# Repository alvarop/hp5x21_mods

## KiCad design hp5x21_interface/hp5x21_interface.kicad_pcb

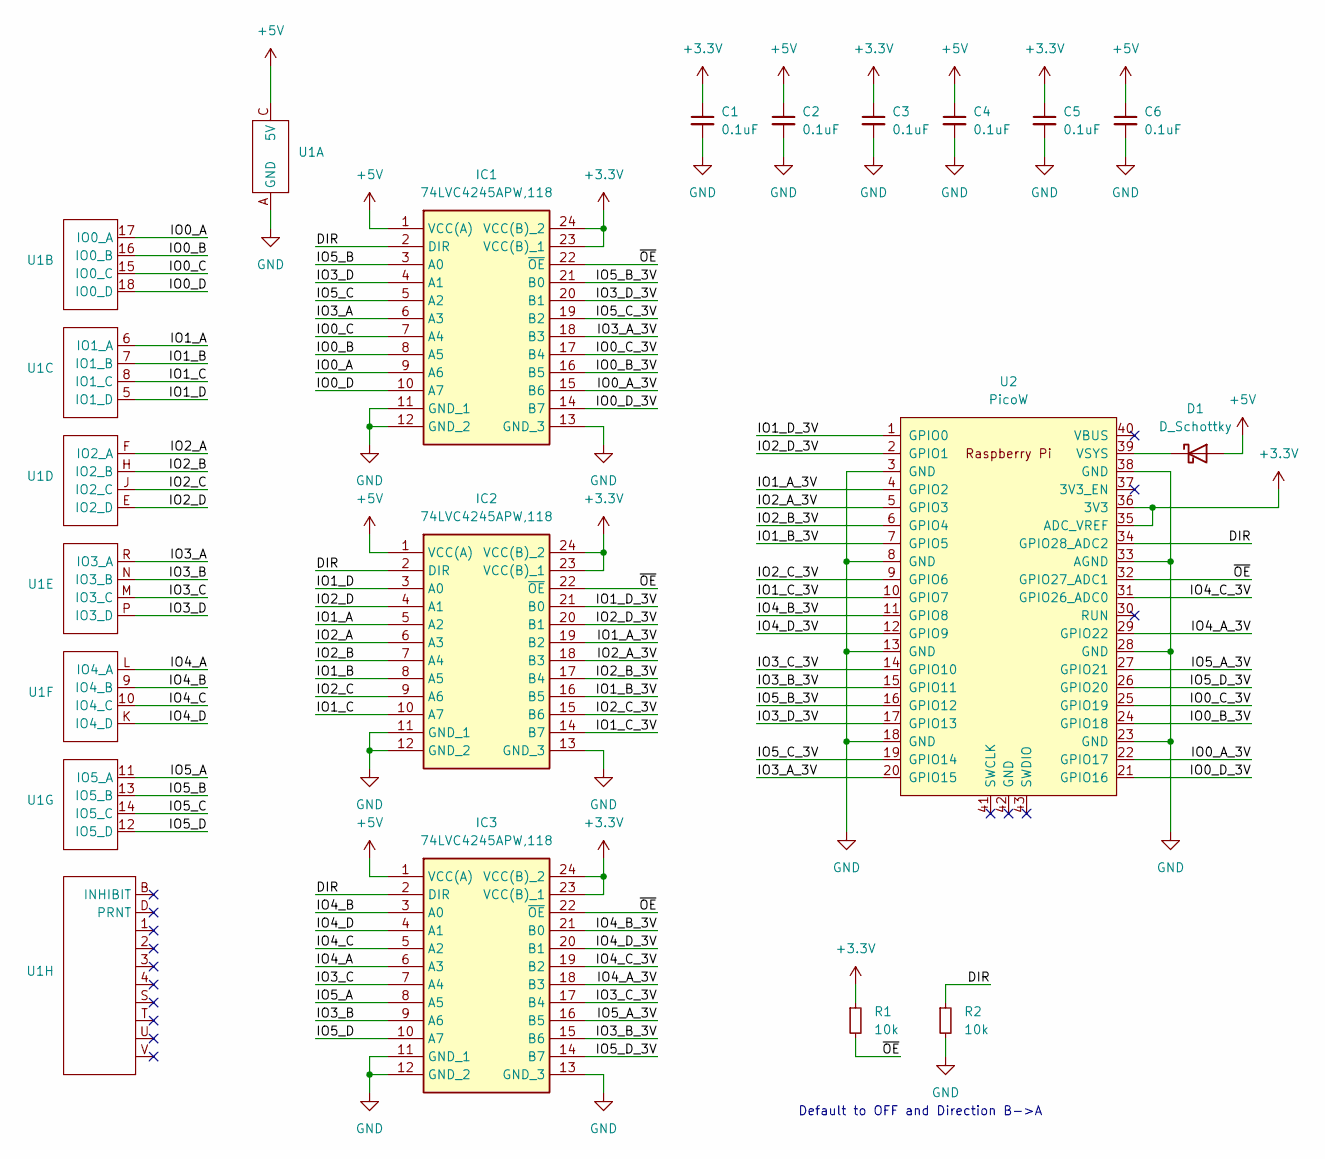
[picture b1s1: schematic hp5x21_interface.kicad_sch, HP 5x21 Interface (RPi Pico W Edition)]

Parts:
C1, C2, C3, C4, C5, C6: 0.1uF; C_0402_1005Metric
D1: D_Schottky; D_SOD-123; MPN MBR0520LT1G
IC1, IC2, IC3: 74LVC4245APW,118; SOP65P640X110-24N; MPN 74LVC4245APW,118
R1, R2: 10k; R_0402_1005Metric
U1: 307-036-520-201; 305-036-520-202; MPN 305-036-520-202
U2: PicoW; RPi_PicoW_SMD_TH; MPN SC0918

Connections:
+3.3V: C1.1, C3.1, C5.1, IC1.23 (VCC(B)_1), IC1.24 (VCC(B)_2), IC2.23 (VCC(B)_1), IC2.24 (VCC(B)_2), IC3.23 (VCC(B)_1), IC3.24 (VCC(B)_2), R1.1, U2.35 (ADC_VREF), U2.36 (3V3)
+5V: C2.1, C4.1, C6.1, D1.2 (A), IC1.1 (VCC(A)), IC2.1 (VCC(A)), IC3.1 (VCC(A)), U1.C (5V)
/DIR: IC1.2 (DIR), IC2.2 (DIR), IC3.2 (DIR), R2.1, U2.34 (GPIO28_ADC2)
/IO0_A: IC1.9 (A6), U1.17 (IO0_A)
/IO0_A_3V: IC1.15 (B6), U2.22 (GPIO17)
/IO0_B: IC1.8 (A5), U1.16 (IO0_B)
/IO0_B_3V: IC1.16 (B5), U2.24 (GPIO18)
/IO0_C: IC1.7 (A4), U1.15 (IO0_C)
/IO0_C_3V: IC1.17 (B4), U2.25 (GPIO19)
/IO0_D: IC1.10 (A7), U1.18 (IO0_D)
/IO0_D_3V: IC1.14 (B7), U2.21 (GPIO16)
/IO1_A: IC2.5 (A2), U1.6 (IO1_A)
/IO1_A_3V: IC2.19 (B2), U2.4 (GPIO2)
/IO1_B: IC2.8 (A5), U1.7 (IO1_B)
/IO1_B_3V: IC2.16 (B5), U2.7 (GPIO5)
/IO1_C: IC2.10 (A7), U1.8 (IO1_C)
/IO1_C_3V: IC2.14 (B7), U2.10 (GPIO7)
/IO1_D: IC2.3 (A0), U1.5 (IO1_D)
/IO1_D_3V: IC2.21 (B0), U2.1 (GPIO0)
/IO2_A: IC2.6 (A3), U1.F (IO2_A)
/IO2_A_3V: IC2.18 (B3), U2.5 (GPIO3)
/IO2_B: IC2.7 (A4), U1.H (IO2_B)
/IO2_B_3V: IC2.17 (B4), U2.6 (GPIO4)
/IO2_C: IC2.9 (A6), U1.J (IO2_C)
/IO2_C_3V: IC2.15 (B6), U2.9 (GPIO6)
/IO2_D: IC2.4 (A1), U1.E (IO2_D)
/IO2_D_3V: IC2.20 (B1), U2.2 (GPIO1)
/IO3_A: IC1.6 (A3), U1.R (IO3_A)
/IO3_A_3V: IC1.18 (B3), U2.20 (GPIO15)
/IO3_B: IC3.9 (A6), U1.N (IO3_B)
/IO3_B_3V: IC3.15 (B6), U2.15 (GPIO11)
/IO3_C: IC3.7 (A4), U1.M (IO3_C)
/IO3_C_3V: IC3.17 (B4), U2.14 (GPIO10)
/IO3_D: IC1.4 (A1), U1.P (IO3_D)
/IO3_D_3V: IC1.20 (B1), U2.17 (GPIO13)
/IO4_A: IC3.6 (A3), U1.L (IO4_A)
/IO4_A_3V: IC3.18 (B3), U2.29 (GPIO22)
/IO4_B: IC3.3 (A0), U1.9 (IO4_B)
/IO4_B_3V: IC3.21 (B0), U2.11 (GPIO8)
/IO4_C: IC3.5 (A2), U1.10 (IO4_C)
/IO4_C_3V: IC3.19 (B2), U2.31 (GPIO26_ADC0)
/IO4_D: IC3.4 (A1), U1.K (IO4_D)
/IO4_D_3V: IC3.20 (B1), U2.12 (GPIO9)
/IO5_A: IC3.8 (A5), U1.11 (IO5_A)
/IO5_A_3V: IC3.16 (B5), U2.27 (GPIO21)
/IO5_B: IC1.3 (A0), U1.13 (IO5_B)
/IO5_B_3V: IC1.21 (B0), U2.16 (GPIO12)
/IO5_C: IC1.5 (A2), U1.14 (IO5_C)
/IO5_C_3V: IC1.19 (B2), U2.19 (GPIO14)
/IO5_D: IC3.10 (A7), U1.12 (IO5_D)
/IO5_D_3V: IC3.14 (B7), U2.26 (GPIO20)
/~OE: IC1.22 (~OE), IC2.22 (~OE), IC3.22 (~OE), R1.2, U2.32 (GPIO27_ADC1)
GND: C1.2, C2.2, C3.2, C4.2, C5.2, C6.2, IC1.11 (GND_1), IC1.12 (GND_2), IC1.13 (GND_3), IC2.11 (GND_1), IC2.12 (GND_2), IC2.13 (GND_3), IC3.11 (GND_1), IC3.12 (GND_2), IC3.13 (GND_3), R2.2, U1.A (GND), U2.3 (GND), U2.8 (GND), U2.13 (GND), U2.18 (GND), U2.23 (GND), U2.28 (GND), U2.33 (AGND), U2.38 (GND)
unnamed: D1.1 (K), U2.39 (VSYS)

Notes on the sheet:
Default to OFF and Direction B->A

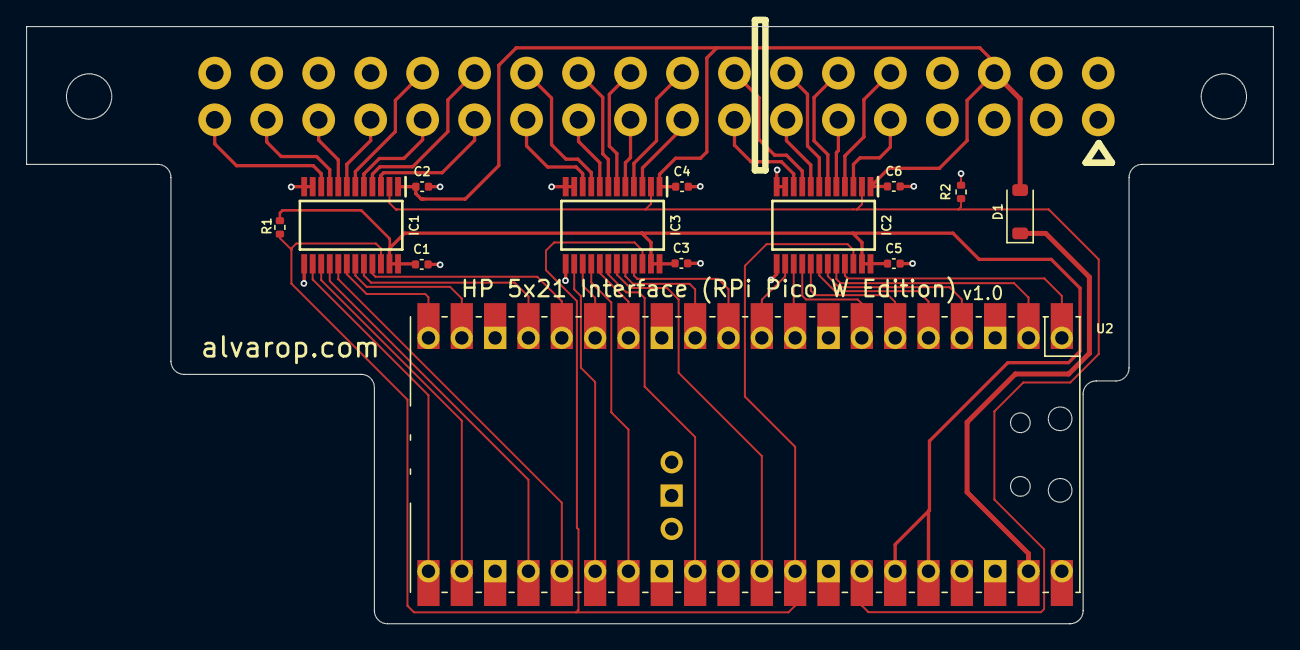
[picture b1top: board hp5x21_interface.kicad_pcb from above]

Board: 2 copper layers, 95.0 x 45.5 mm, 14 parts (1 on the bottom side), 54 nets.

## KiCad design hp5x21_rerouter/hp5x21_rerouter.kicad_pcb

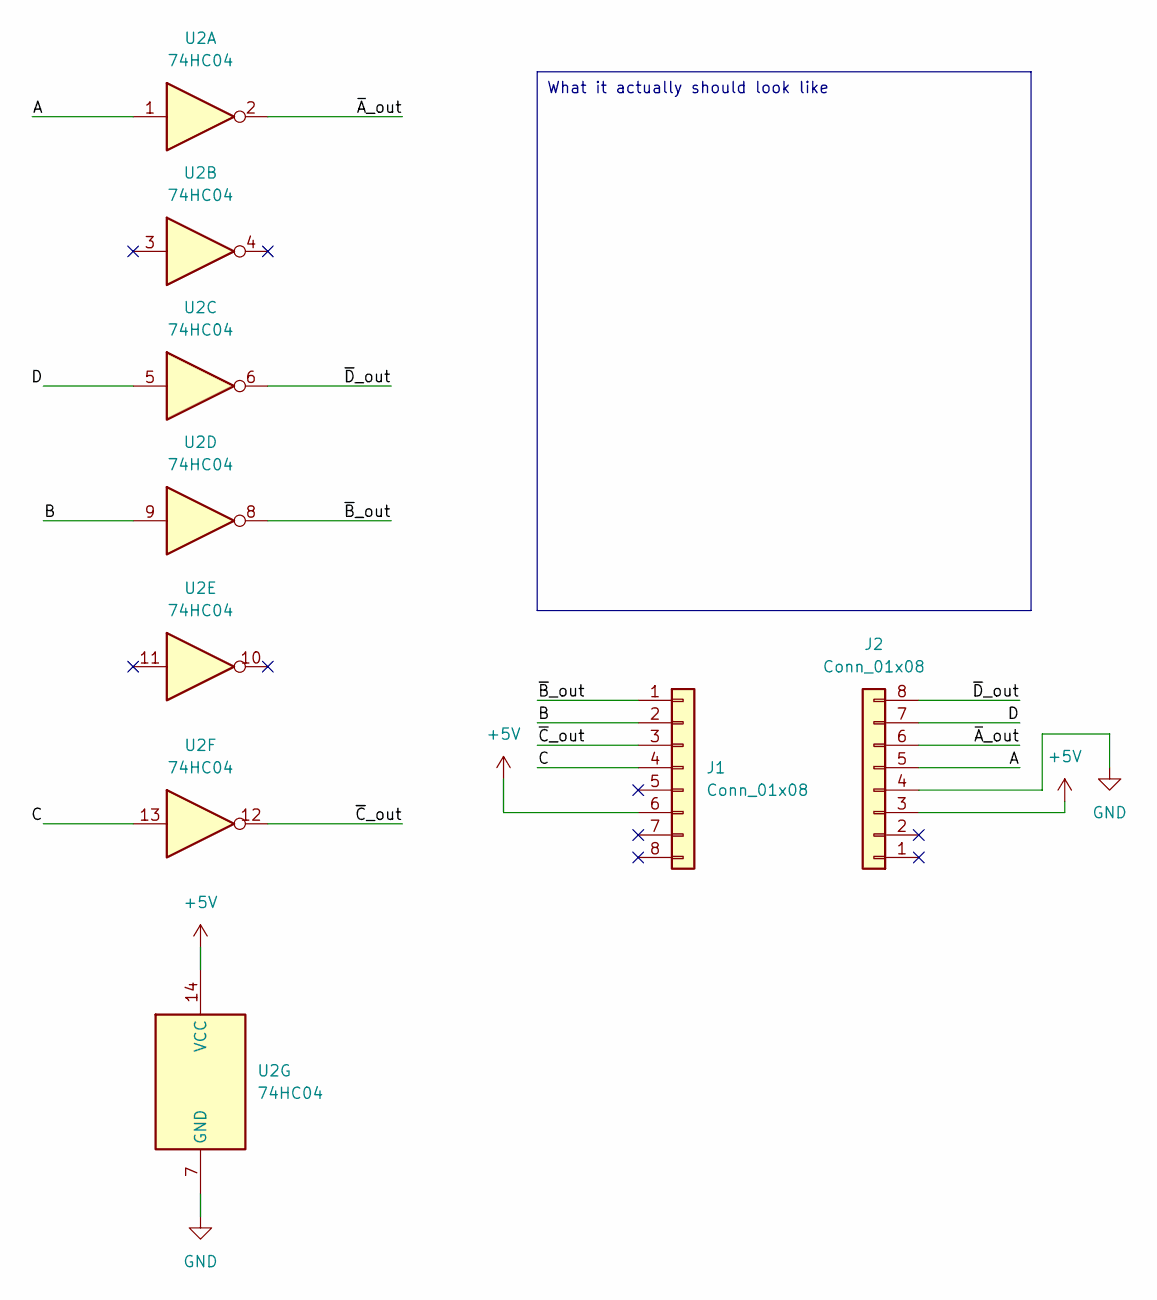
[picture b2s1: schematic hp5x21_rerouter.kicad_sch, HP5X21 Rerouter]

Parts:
J1: Conn_01x08; PinHeader_1x08_P2.54mm_Vertical_nosilk; LCSC C18078205
J2: Conn_01x08; PinHeader_1x08_P2.54mm_Vertical_nosquare; LCSC C18078205
U2: 74HC04; DHVQFN14_2.5x3mm; LCSC C546494

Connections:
+5V: J1.6, J2.3, U2.14 (VCC)
/A: J2.5, U2.1
/B: J1.2, U2.9
/C: J1.4, U2.13
/D: J2.7, U2.5
/~A_out: J2.6, U2.2
/~B_out: J1.1, U2.8
/~C_out: J1.3, U2.12
/~D_out: J2.8, U2.6
GND: J2.4, U2.7 (GND)

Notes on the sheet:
What it actually should look like

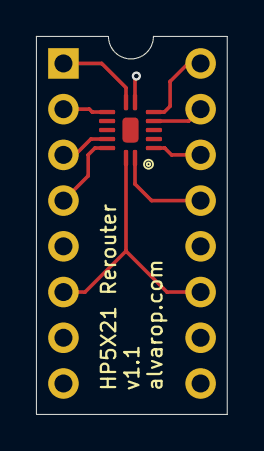
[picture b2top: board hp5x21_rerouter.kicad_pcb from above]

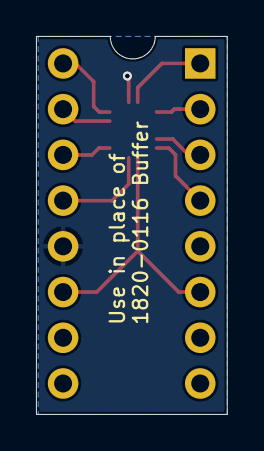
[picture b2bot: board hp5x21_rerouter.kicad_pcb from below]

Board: 2 copper layers, 10.6 x 21.0 mm, 3 parts (2 on the bottom side), 10 nets.

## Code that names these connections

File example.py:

"""
Example micropython program to run as a clock

Set the time with `mpremote connect port:/dev/ttyACM0 rtc --set`
Run with `mpremote connect port:/dev/ttyACM1 run example.py`

"""

import time
import machine

led = machine.Pin("LED", machine.Pin.OUT)
rtc = machine.RTC()

digits = [
    [
        machine.Pin(17, machine.Pin.OUT),  # IO0_A
        machine.Pin(18, machine.Pin.OUT),  # IO0_B
        machine.Pin(19, machine.Pin.OUT),  # IO0_C
        machine.Pin(16, machine.Pin.OUT),  # IO0_D
    ],
    [
        machine.Pin(2, machine.Pin.OUT),  # IO1_A
        machine.Pin(5, machine.Pin.OUT),  # IO1_B
        machine.Pin(7, machine.Pin.OUT),  # IO1_C
        machine.Pin(0, machine.Pin.OUT),  # IO1_D
    ],
    [
        machine.Pin(3, machine.Pin.OUT),  # IO2_A
        machine.Pin(4, machine.Pin.OUT),  # IO2_B
        machine.Pin(6, machine.Pin.OUT),  # IO2_C
        machine.Pin(1, machine.Pin.OUT),  # IO2_D
    ],
    [
        machine.Pin(15, machine.Pin.OUT),  # IO3_A
        machine.Pin(11, machine.Pin.OUT),  # IO3_B
        machine.Pin(10, machine.Pin.OUT),  # IO3_C
        machine.Pin(13, machine.Pin.OUT),  # IO3_D
    ],
    [
        machine.Pin(22, machine.Pin.OUT),  # IO4_A
        machine.Pin(8, machine.Pin.OUT),  # IO4_B
        machine.Pin(26, machine.Pin.OUT),  # IO4_C
        machine.Pin(9, machine.Pin.OUT),  # IO4_D
    ],
    [
        machine.Pin(21, machine.Pin.OUT),  # IO5_A
        machine.Pin(12, machine.Pin.OUT),  # IO5_B
        machine.Pin(14, machine.Pin.OUT),  # IO5_C
        machine.Pin(20, machine.Pin.OUT),  # IO5_D
    ],
]

def initialize_pins():
    for digit in digits:
        for bit in digit:
            bit.on()

    # dir_pin = machine.Pin(28, machine.Pin.OUT)
    oe_pin = machine.Pin(27, machine.Pin.OUT)

    # dir_pin.off()
    oe_pin.off()

def set_digit(digit, value):
    if value is None or value > 9:
        value = 0xF

    for idx, bit in enumerate(digits[digit]):
        if value & (1 << idx):
            bit.on()
        else:
            bit.off()

def set_digits(value):
    val_str = f"{value:>6}"
    
    for idx, val in enumerate(reversed(val_str)):
        if val in "0123456789":
            set_digit(idx, int(val))
        else:
            set_digit(idx, None)

initialize_pins()

while True:
    year, month, day, weekday, hour, minute, second, subsecond = rtc.datetime()
    set_digits(f"{hour:02}{minute:02}{second:02}")
    time.sleep(0.5)

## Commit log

2025-03-30 Start working on interface board
2025-04-17 Updated and released to JLCPCB
2025-04-29 Minor updates
2025-04-29 Add example.py
